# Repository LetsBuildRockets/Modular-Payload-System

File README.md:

# Cloning

This repo uses submodules. Be sure to clone the submodules as well as the repo:

```sh
git clone https://github.com/LetsBuildRockets/Modular-Payload-System/
cd Modular-Payload-System
git submodule update --init --recursive
```

# Specifications

The Modular Payload System specifications can be found [here](https://github.com/LetsBuildRockets/Modular-Payload-System/blob/master/Hardware/Reference/Specifications.md).

# Modules

A list of modules can be found [here](https://github.com/LetsBuildRockets/Modular-Payload-System/blob/master/ModuleList.md).

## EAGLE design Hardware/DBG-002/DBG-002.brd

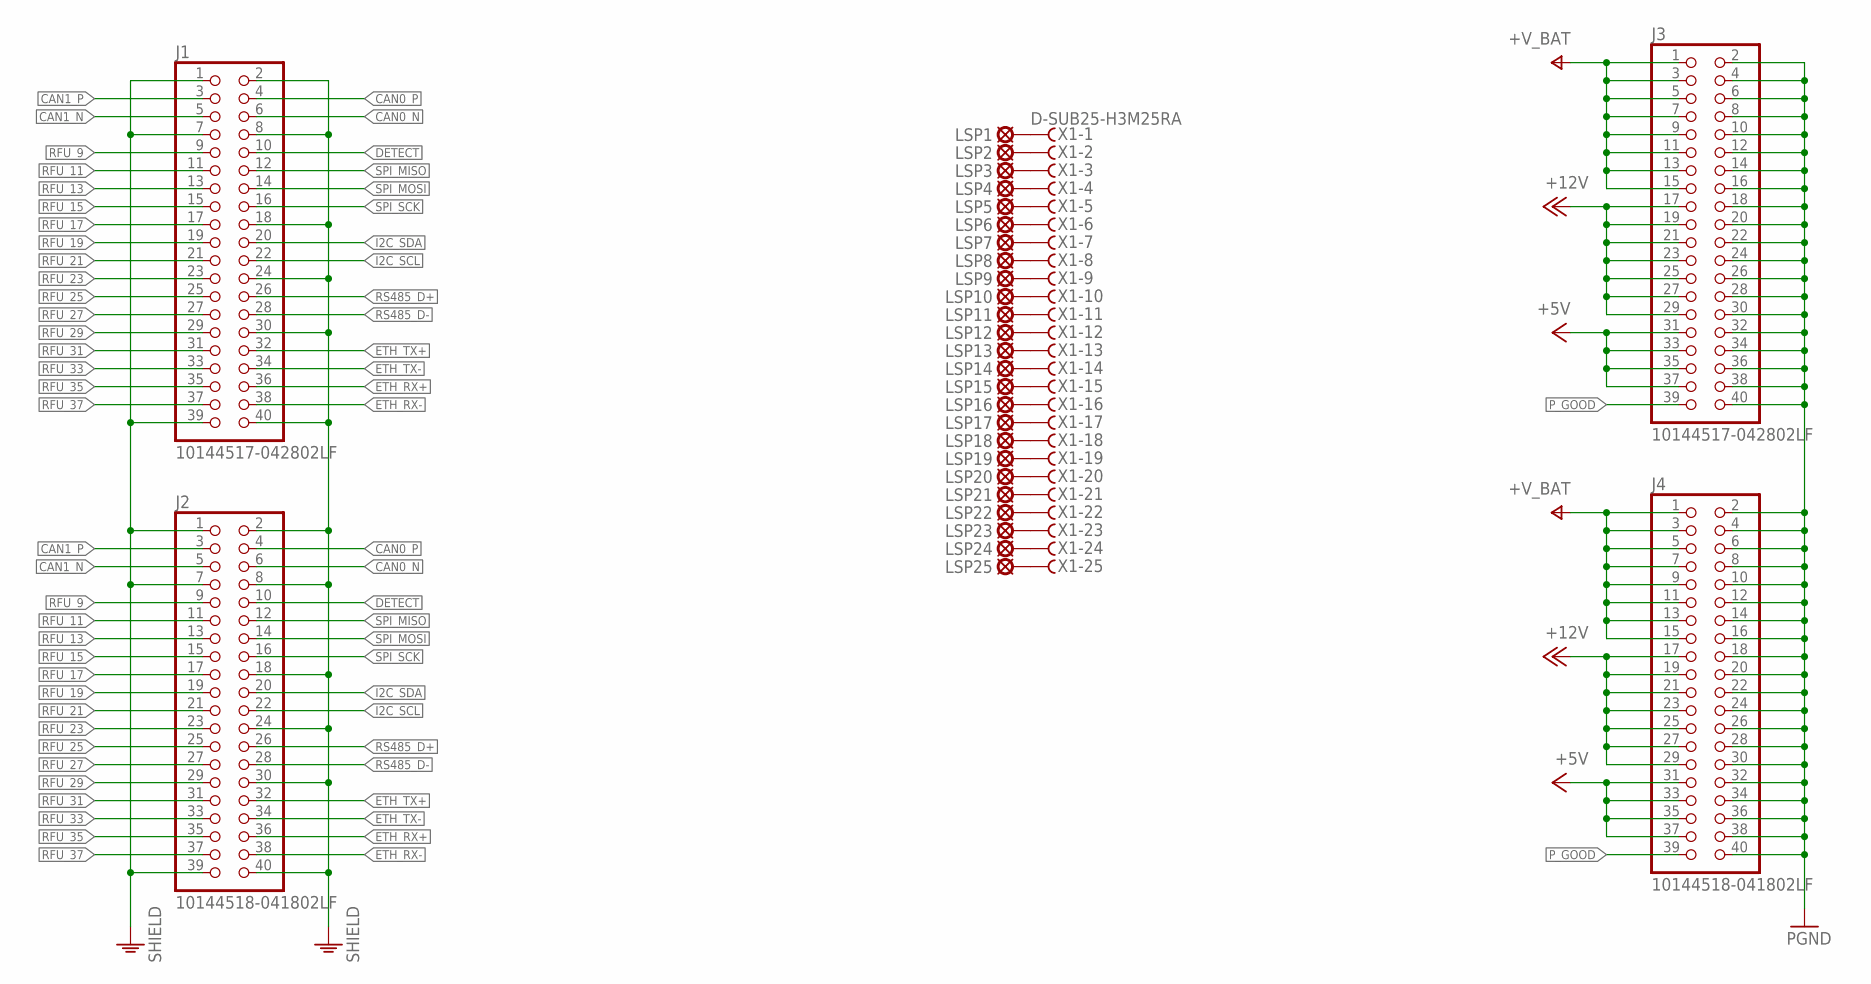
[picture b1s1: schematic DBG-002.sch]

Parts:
J1, J3: 10144517-042802LF
J2, J4: 10144518-041802LF
LSP1, LSP2, LSP3, LSP4, LSP5, LSP6, LSP7, LSP8, LSP9, LSP10, LSP11, LSP12, LSP13, LSP14, LSP15, LSP16, LSP17, LSP18, LSP19, LSP20, LSP21, LSP22, LSP23, LSP24, LSP25: LSP11
X1: D-SUB25-H3M25RA; H3M25RA

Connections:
+5V: J3.31, J3.33, J3.35, J3.37, J4.31, J4.33, J4.35, J4.37
+12V: J3.17, J3.19, J3.21, J3.23, J3.25, J3.27, J3.29, J4.17, J4.19, J4.21, J4.23, J4.25, J4.27, J4.29
+V_BAT: J3.1, J3.3, J3.5, J3.7, J3.9, J3.11, J3.13, J3.15, J4.1, J4.3, J4.5, J4.7, J4.9, J4.11, J4.13, J4.15
CAN0_N: J1.6, J2.6
CAN0_P: J1.4, J2.4
CAN1_N: J1.5, J2.5
CAN1_P: J1.3, J2.3
DETECT: J1.10, J2.10
ETH_RX+: J1.36, J2.36
ETH_RX-: J1.38, J2.38
ETH_TX+: J1.32, J2.32
ETH_TX-: J1.34, J2.34
I2C_SCL: J1.22, J2.22
I2C_SDA: J1.20, J2.20
unnamed: LSP1.MP, X1.1
unnamed: LSP2.MP, X1.2
unnamed: LSP3.MP, X1.3
unnamed: LSP4.MP, X1.4
unnamed: LSP5.MP, X1.5
unnamed: LSP6.MP, X1.6
unnamed: LSP7.MP, X1.7
unnamed: LSP8.MP, X1.8
unnamed: LSP9.MP, X1.9
unnamed: LSP10.MP, X1.10
unnamed: LSP11.MP, X1.11
unnamed: LSP12.MP, X1.12
unnamed: LSP13.MP, X1.13
unnamed: LSP14.MP, X1.14
unnamed: LSP15.MP, X1.15
unnamed: LSP16.MP, X1.16
unnamed: LSP17.MP, X1.17
unnamed: LSP18.MP, X1.18
unnamed: LSP19.MP, X1.19
unnamed: LSP20.MP, X1.20
unnamed: LSP21.MP, X1.21
unnamed: LSP22.MP, X1.22
unnamed: LSP23.MP, X1.23
unnamed: LSP24.MP, X1.24
unnamed: LSP25.MP, X1.25
PGND: J3.2, J3.4, J3.6, J3.8, J3.10, J3.12, J3.14, J3.16, J3.18, J3.20, J3.22, J3.24, J3.26, J3.28, J3.30, J3.32, J3.34, J3.36, J3.38, J3.40, J4.2, J4.4, J4.6, J4.8, J4.10, J4.12, J4.14, J4.16, J4.18, J4.20, J4.22, J4.24, J4.26, J4.28, J4.30, J4.32, J4.34, J4.36, J4.38, J4.40
P_GOOD: J3.39, J4.39
RFU_9: J1.9, J2.9
RFU_11: J1.11, J2.11
RFU_13: J1.13, J2.13
RFU_15: J1.15, J2.15
RFU_17: J1.17, J2.17
RFU_19: J1.19, J2.19
RFU_21: J1.21, J2.21
RFU_23: J1.23, J2.23
RFU_25: J1.25, J2.25
RFU_27: J1.27, J2.27
RFU_29: J1.29, J2.29
RFU_31: J1.31, J2.31
RFU_33: J1.33, J2.33
RFU_35: J1.35, J2.35
RFU_37: J1.37, J2.37
RS485_D+: J1.26, J2.26
RS485_D-: J1.28, J2.28
SHIELD: J1.1, J1.2, J1.7, J1.8, J1.18, J1.24, J1.30, J1.39, J1.40, J2.1, J2.2, J2.7, J2.8, J2.18, J2.24, J2.30, J2.39, J2.40
SPI_MISO: J1.12, J2.12
SPI_MOSI: J1.14, J2.14
SPI_SCK: J1.16, J2.16

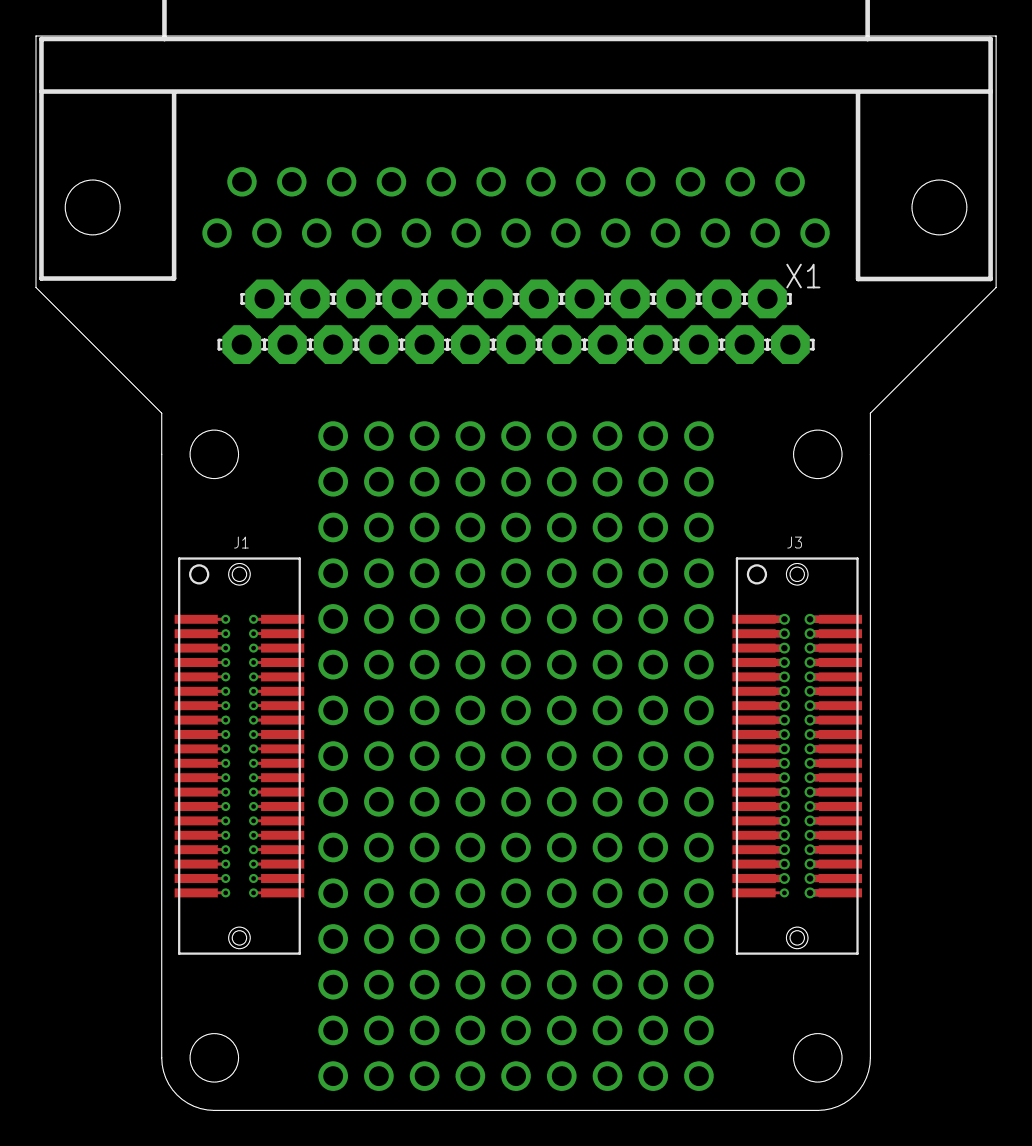
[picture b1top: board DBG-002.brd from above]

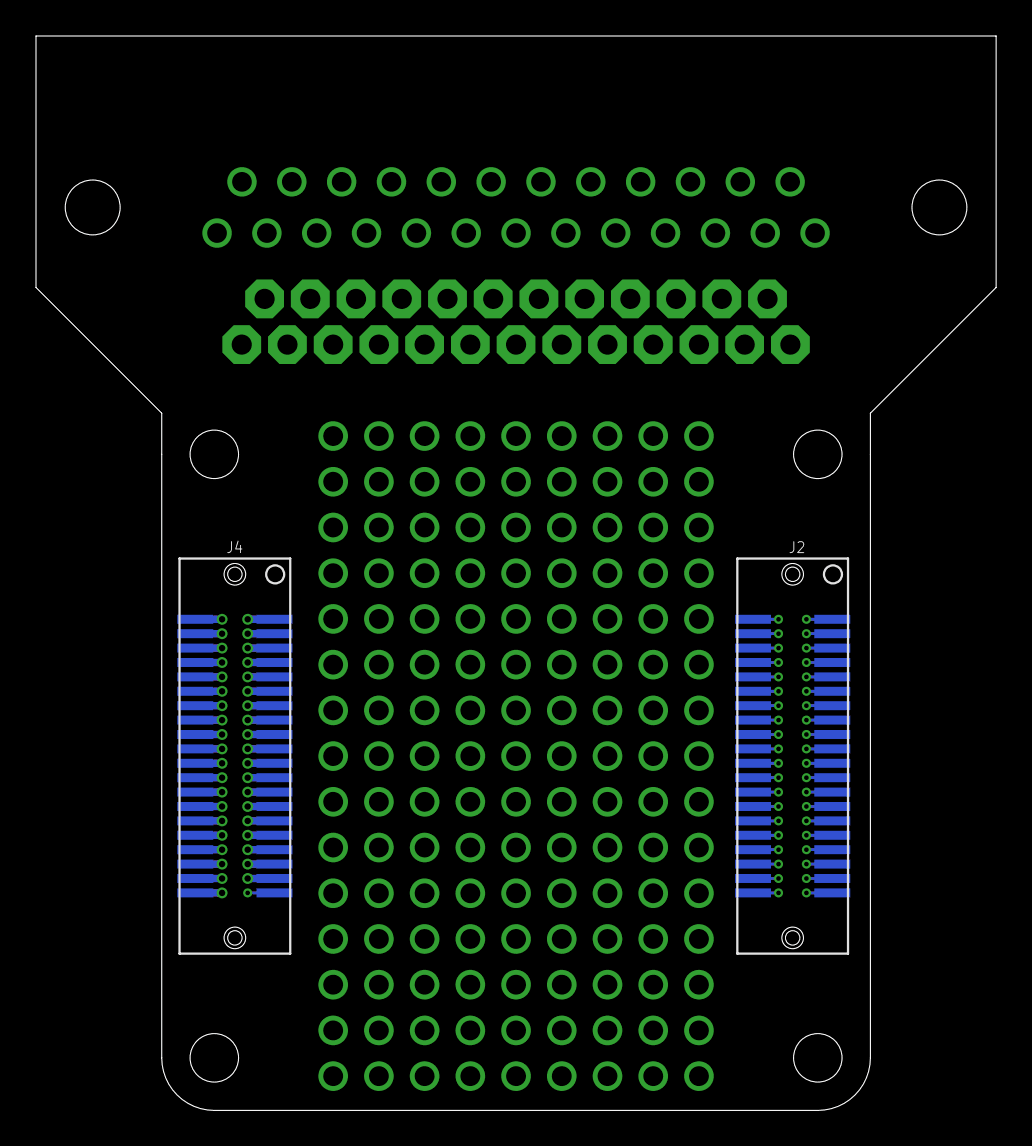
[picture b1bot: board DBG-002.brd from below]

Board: 2 copper layers, 53.3 x 59.7 mm, 30 parts (2 on the bottom side), 62 nets.

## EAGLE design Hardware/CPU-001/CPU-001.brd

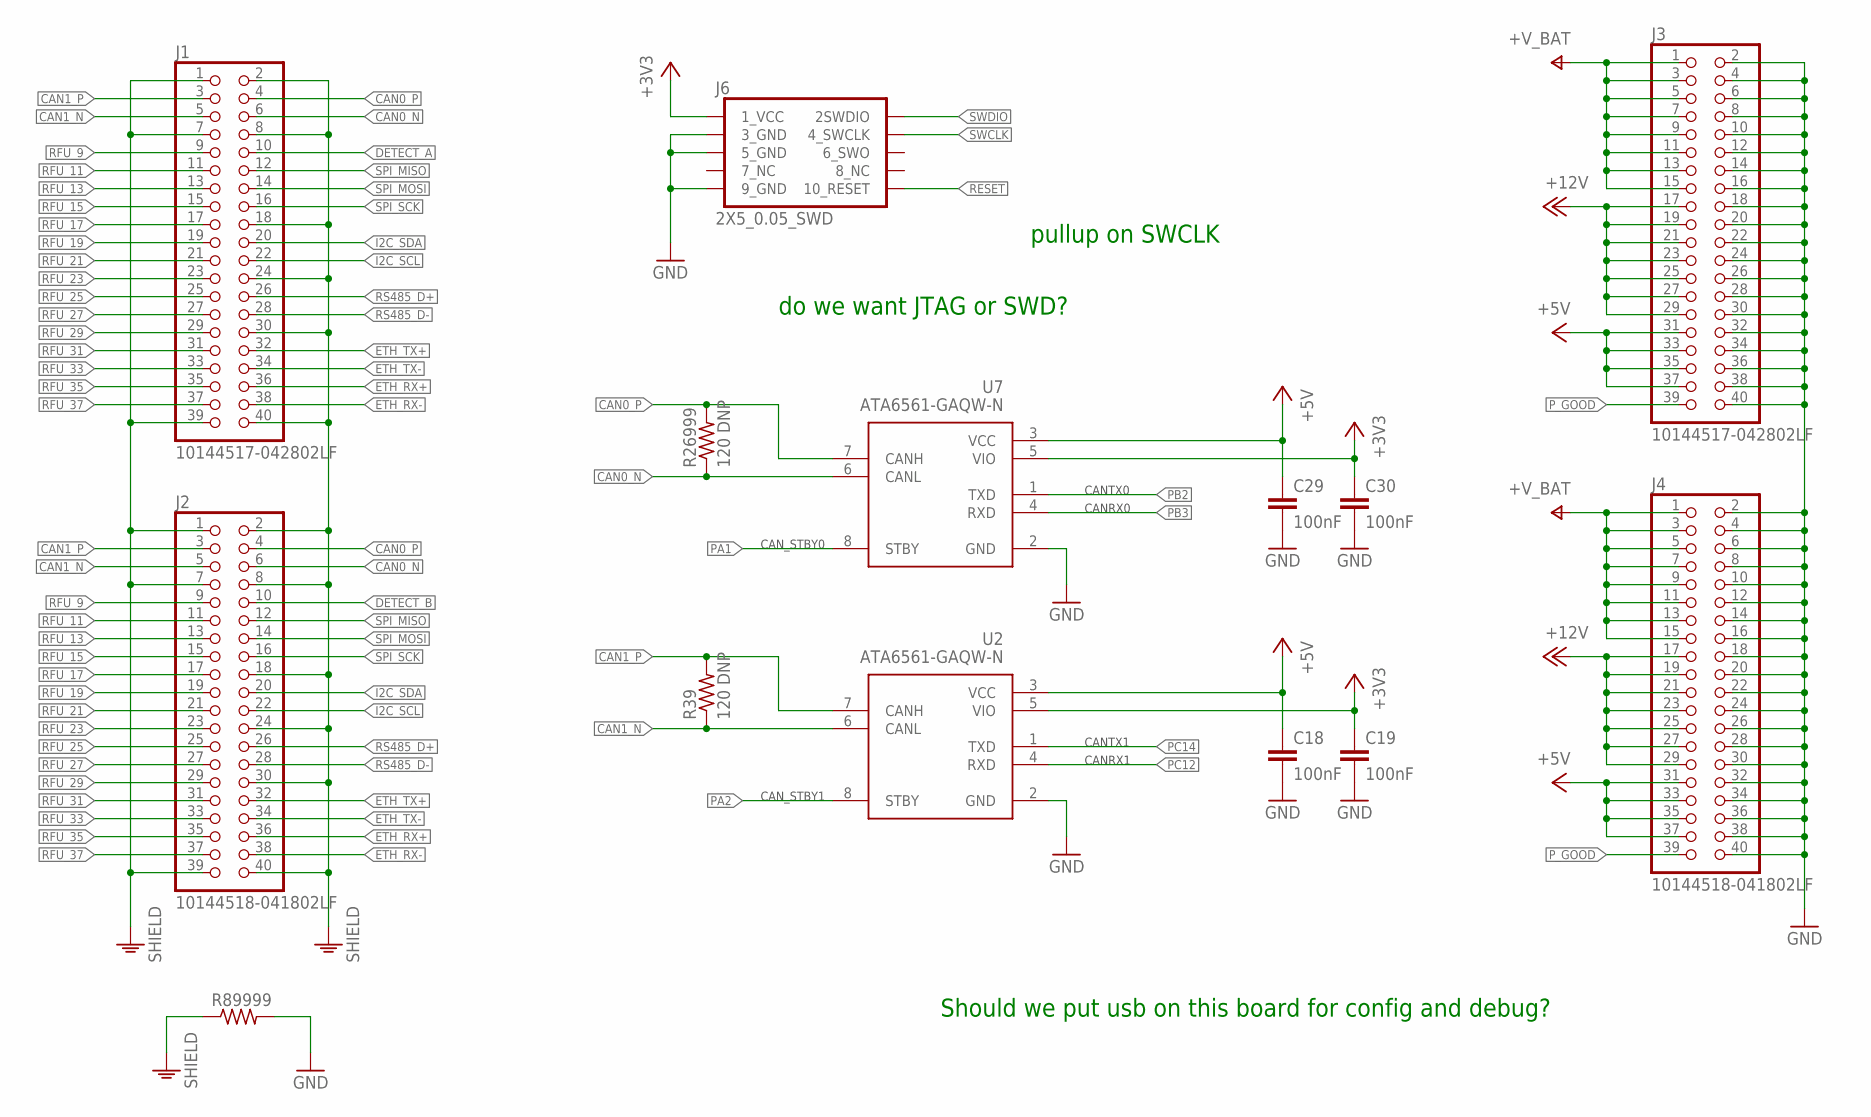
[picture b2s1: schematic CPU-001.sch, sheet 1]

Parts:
C18, C19, C29, C30: 100nF; C0402
J1, J3: 10144517-042802LF
J2, J4: 10144518-041802LF
J6: 2X5_0.05_SWD; 2X5_RIGHT
R39, R26999: 120 DNP; R0402
R89999: R-US_R0402; R0402
U2, U7: ATA6561-GAQW-N; SOIC127P600X175-8N

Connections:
+3V3: C19.1, C30.1, J6.1 (1_VCC), U2.5 (VIO), U7.5 (VIO); also elsewhere on the board
+5V: C18.1, C29.1, J3.31, J3.33, J3.35, J3.37, J4.31, J4.33, J4.35, J4.37, U2.3 (VCC), U7.3 (VCC); also elsewhere on the board
+12V: J3.17, J3.19, J3.21, J3.23, J3.25, J3.27, J3.29, J4.17, J4.19, J4.21, J4.23, J4.25, J4.27, J4.29
+V_BAT: J3.1, J3.3, J3.5, J3.7, J3.9, J3.11, J3.13, J3.15, J4.1, J4.3, J4.5, J4.7, J4.9, J4.11, J4.13, J4.15
CAN0_N: J1.6, J2.6, R26999.1, U7.6 (CANL)
CAN0_P: J1.4, J2.4, R26999.2, U7.7 (CANH)
CAN1_N: J1.5, J2.5, R39.1, U2.6 (CANL)
CAN1_P: J1.3, J2.3, R39.2, U2.7 (CANH)
DETECT_A: J1.10
DETECT_B: J2.10
ETH_RX+: J1.36, J2.36
ETH_RX-: J1.38, J2.38
ETH_TX+: J1.32, J2.32
ETH_TX-: J1.34, J2.34
GND: C18.2, C19.2, C29.2, C30.2, J3.2, J3.4, J3.6, J3.8, J3.10, J3.12, J3.14, J3.16, J3.18, J3.20, J3.22, J3.24, J3.26, J3.28, J3.30, J3.32, J3.34, J3.36, J3.38, J3.40, J4.2, J4.4, J4.6, J4.8, J4.10, J4.12, J4.14, J4.16, J4.18, J4.20, J4.22, J4.24, J4.26, J4.28, J4.30, J4.32, J4.34, J4.36, J4.38, J4.40, J6.3 (3_GND), J6.5 (5_GND), J6.9 (9_GND), R89999.2, U2.2 (GND), U7.2 (GND); also elsewhere on the board
I2C_SCL: J1.22, J2.22
I2C_SDA: J1.20, J2.20
PA1: U7.8 (STBY); also elsewhere on the board
PA2: U2.8 (STBY); also elsewhere on the board
PB2: U7.1 (TXD); also elsewhere on the board
PB3: U7.4 (RXD); also elsewhere on the board
PC12: U2.4 (RXD); also elsewhere on the board
PC14: U2.1 (TXD); also elsewhere on the board
P_GOOD: J3.39, J4.39
RESET: J6.10 (10_RESET)
RFU_9: J1.9, J2.9
RFU_11: J1.11, J2.11
RFU_13: J1.13, J2.13
RFU_15: J1.15, J2.15
RFU_17: J1.17, J2.17
RFU_19: J1.19, J2.19
RFU_21: J1.21, J2.21
RFU_23: J1.23, J2.23
RFU_25: J1.25, J2.25
RFU_27: J1.27, J2.27
RFU_29: J1.29, J2.29
RFU_31: J1.31, J2.31
RFU_33: J1.33, J2.33
RFU_35: J1.35, J2.35
RFU_37: J1.37, J2.37
RS485_D+: J1.26, J2.26
RS485_D-: J1.28, J2.28
SHIELD: J1.1, J1.2, J1.7, J1.8, J1.18, J1.24, J1.30, J1.39, J1.40, J2.1, J2.2, J2.7, J2.8, J2.18, J2.24, J2.30, J2.39, J2.40, R89999.1
SPI_MISO: J1.12, J2.12
SPI_MOSI: J1.14, J2.14
SPI_SCK: J1.16, J2.16
SWCLK: J6.4 (4_SWCLK)
SWDIO: J6.2 (2SWDIO)

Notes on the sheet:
do we want JTAG or SWD?
Should we put usb on this board for config and debug?
pullup on SWCLK
CAN_STBY0
CAN_STBY1
CANTX0
CANRX0
CANRX1
CANTX1

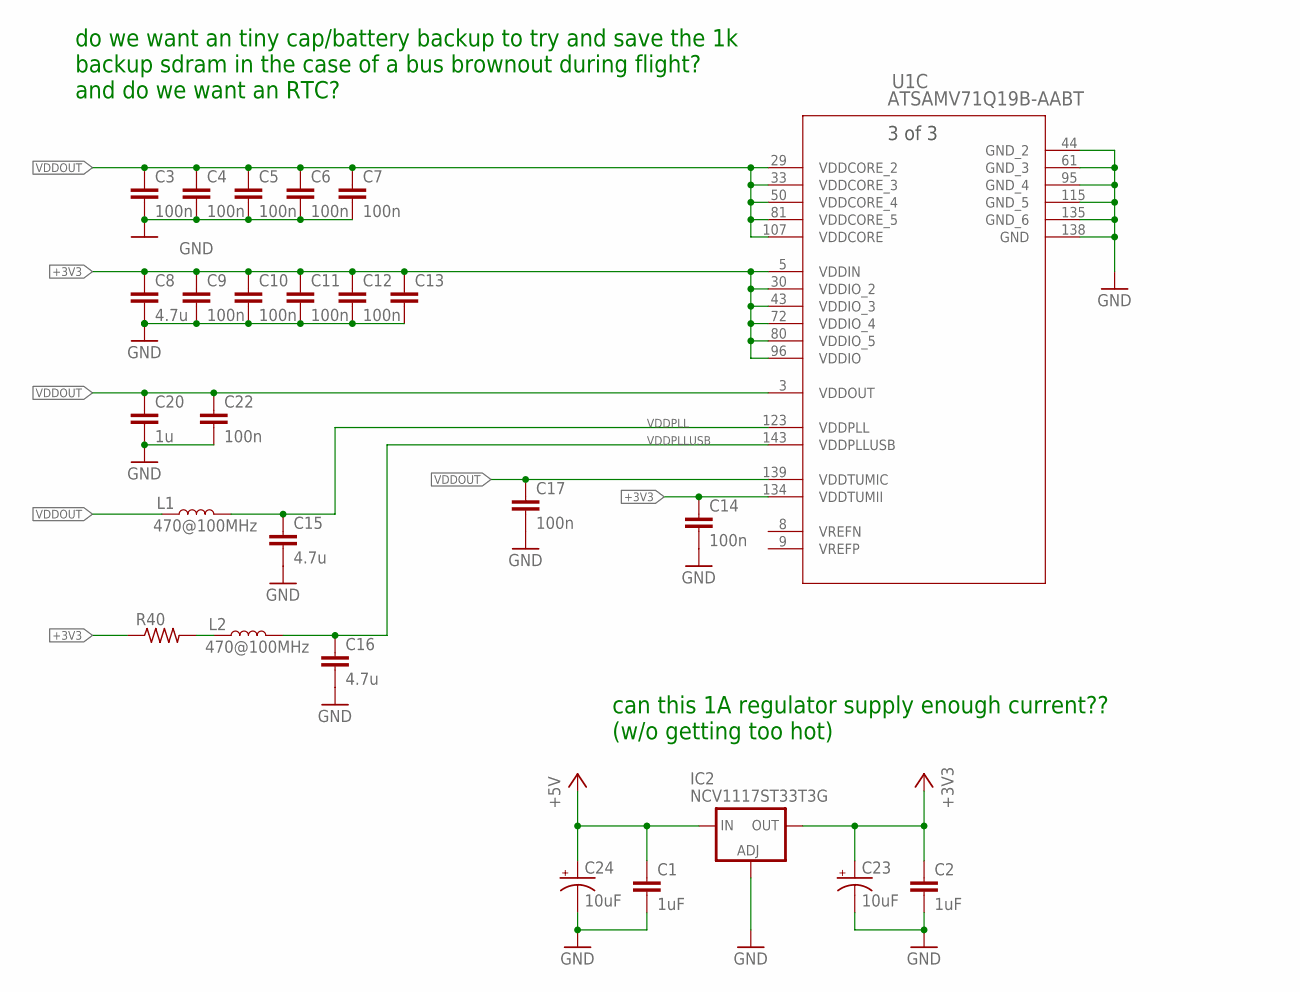
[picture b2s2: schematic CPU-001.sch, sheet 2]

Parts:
C1, C2: 1uF; C0603
C3, C4, C5, C6, C7, C9, C10, C11, C12, C13, C14, C17, C22: 100n; C0402
C8, C15, C16: 4.7u; C0805
C20: 1u; C0402
C23, C24: 10uF; 0603-POLAR
IC2: NCV1117ST33T3G; SOT223
L1, L2: 470@100MHz; 0603
R40: R-US_R0402; R0402
U1: ATSAMV71Q19B-AABT; LQFP144_20X20MC

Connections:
+3V3: C2.1, C8.1, C9.1, C10.1, C11.1, C12.1, C13.1, C14.1, C23.+, IC2.4 (OUT), R40.1, U1.5 (VDDIN), U1.30 (VDDIO_2), U1.43 (VDDIO_3), U1.72 (VDDIO_4), U1.80 (VDDIO_5), U1.96 (VDDIO), U1.134 (VDDTUMII); also elsewhere on the board
+5V: C1.1, C24.+, IC2.3 (IN); also elsewhere on the board
GND: C1.2, C2.2, C3.2, C4.2, C5.2, C6.2, C7.2, C8.2, C9.2, C10.2, C11.2, C12.2, C13.2, C14.2, C15.2, C16.2, C17.2, C20.2, C22.2, C23.-, C24.-, IC2.1 (ADJ), U1.44 (GND_2), U1.61 (GND_3), U1.95 (GND_4), U1.115 (GND_5), U1.135 (GND_6), U1.138 (GND); also elsewhere on the board
unnamed: L2.1, R40.2
VDDOUT: C3.1, C4.1, C5.1, C6.1, C7.1, C17.1, C20.1, C22.1, L1.1, U1.3 (VDDOUT), U1.29 (VDDCORE_2), U1.33 (VDDCORE_3), U1.50 (VDDCORE_4), U1.81 (VDDCORE_5), U1.107 (VDDCORE), U1.139 (VDDTUMIC)
VDDPLL: C15.1, L1.2, U1.123 (VDDPLL)
VDDPLLUSB: C16.1, L2.2, U1.143 (VDDPLLUSB)
VREFN: U1.8 (VREFN)
VREFP: U1.9 (VREFP)

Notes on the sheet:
can this 1A regulator supply enough current?? (w/o getting too hot)
do we want an tiny cap/battery backup to try and save the 1k backup sdram in the case of a bus brownout during flight? and do we want an RTC?

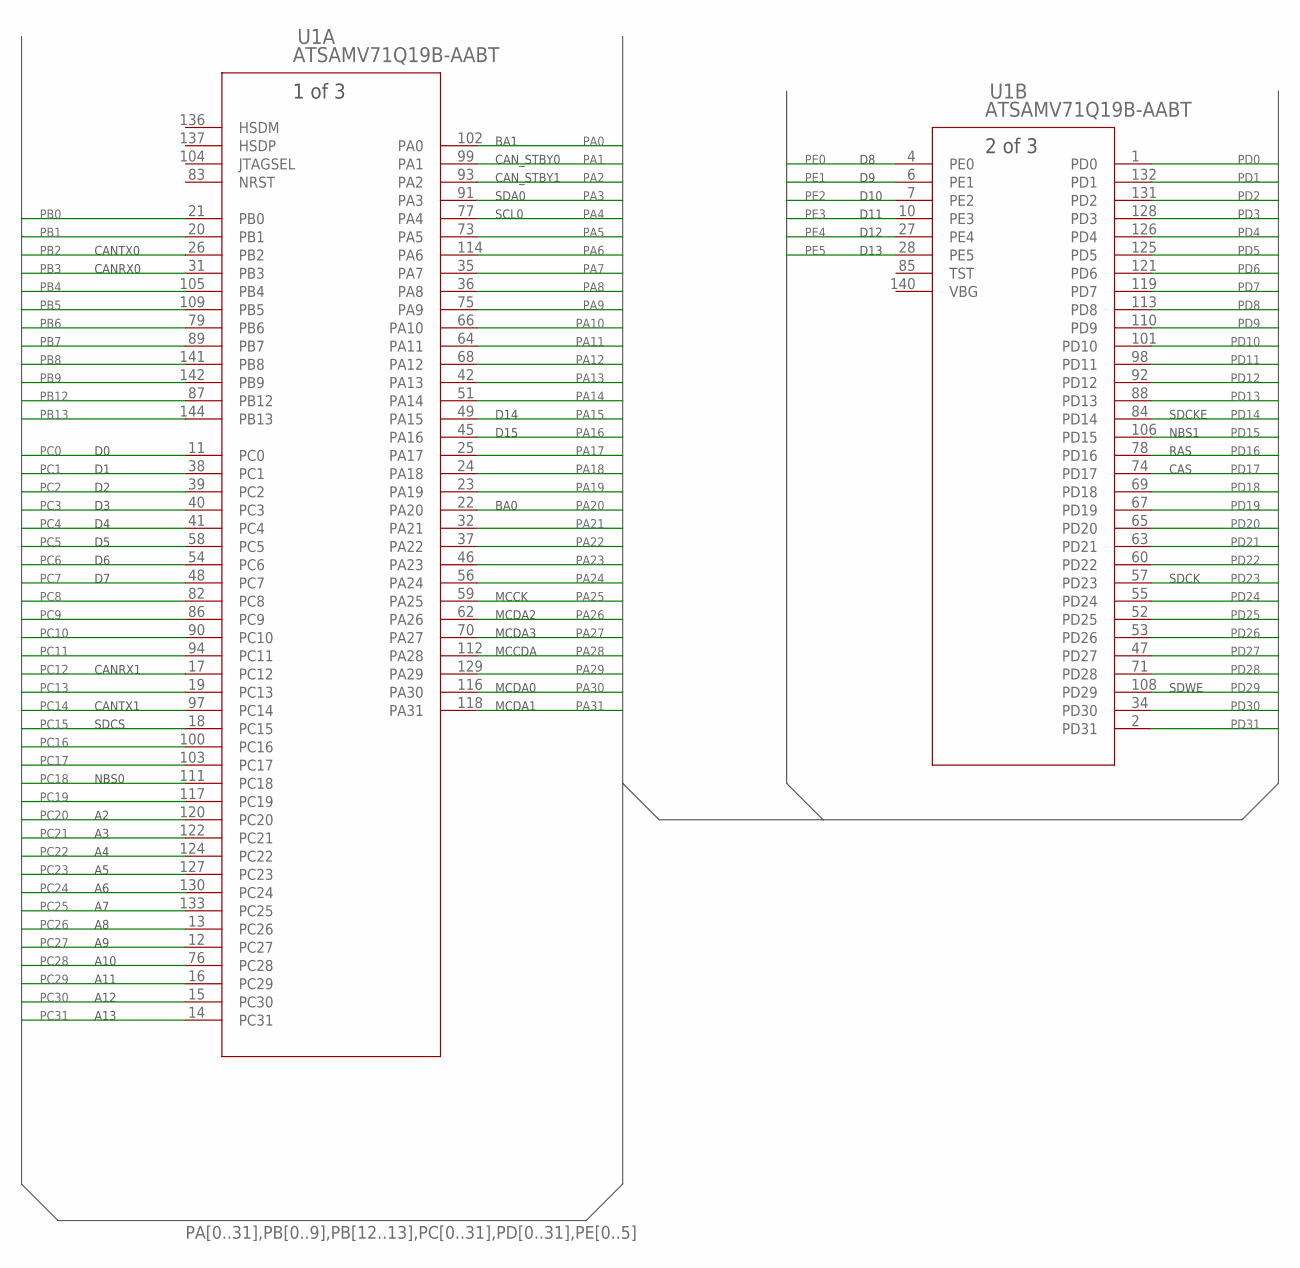
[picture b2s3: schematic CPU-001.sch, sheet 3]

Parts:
U1: ATSAMV71Q19B-AABT; LQFP144_20X20MC

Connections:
PA0: U1.102 (PA0); also elsewhere on the board
PA1: U1.99 (PA1); also elsewhere on the board
PA2: U1.93 (PA2); also elsewhere on the board
PA3: U1.91 (PA3); also elsewhere on the board
PA4: U1.77 (PA4); also elsewhere on the board
PA5: U1.73 (PA5)
PA6: U1.114 (PA6)
PA7: U1.35 (PA7)
PA8: U1.36 (PA8)
PA9: U1.75 (PA9)
PA10: U1.66 (PA10)
PA11: U1.64 (PA11)
PA12: U1.68 (PA12)
PA13: U1.42 (PA13)
PA14: U1.51 (PA14)
PA15: U1.49 (PA15); also elsewhere on the board
PA16: U1.45 (PA16); also elsewhere on the board
PA17: U1.25 (PA17)
PA18: U1.24 (PA18)
PA19: U1.23 (PA19)
PA20: U1.22 (PA20); also elsewhere on the board
PA21: U1.32 (PA21)
PA22: U1.37 (PA22)
PA23: U1.46 (PA23)
PA24: U1.56 (PA24)
PA25: U1.59 (PA25); also elsewhere on the board
PA26: U1.62 (PA26); also elsewhere on the board
PA27: U1.70 (PA27); also elsewhere on the board
PA28: U1.112 (PA28); also elsewhere on the board
PA29: U1.129 (PA29)
PA30: U1.116 (PA30); also elsewhere on the board
PA31: U1.118 (PA31); also elsewhere on the board
PB0: U1.21 (PB0)
PB1: U1.20 (PB1)
PB2: U1.26 (PB2); also elsewhere on the board
PB3: U1.31 (PB3); also elsewhere on the board
PB4: U1.105 (PB4)
PB5: U1.109 (PB5)
PB6: U1.79 (PB6)
PB7: U1.89 (PB7)
PB8: U1.141 (PB8)
PB9: U1.142 (PB9)
PB12: U1.87 (PB12)
PB13: U1.144 (PB13)
PC0: U1.11 (PC0); also elsewhere on the board
PC1: U1.38 (PC1); also elsewhere on the board
PC2: U1.39 (PC2); also elsewhere on the board
PC3: U1.40 (PC3); also elsewhere on the board
PC4: U1.41 (PC4); also elsewhere on the board
PC5: U1.58 (PC5); also elsewhere on the board
PC6: U1.54 (PC6); also elsewhere on the board
PC7: U1.48 (PC7); also elsewhere on the board
PC8: U1.82 (PC8)
PC9: U1.86 (PC9)
PC10: U1.90 (PC10)
PC11: U1.94 (PC11)
PC12: U1.17 (PC12); also elsewhere on the board
PC13: U1.19 (PC13)
PC14: U1.97 (PC14); also elsewhere on the board
PC15: U1.18 (PC15); also elsewhere on the board
PC16: U1.100 (PC16)
PC17: U1.103 (PC17)
PC18: U1.111 (PC18); also elsewhere on the board
PC19: U1.117 (PC19)
PC20: U1.120 (PC20); also elsewhere on the board
PC21: U1.122 (PC21); also elsewhere on the board
PC22: U1.124 (PC22); also elsewhere on the board
PC23: U1.127 (PC23); also elsewhere on the board
PC24: U1.130 (PC24); also elsewhere on the board
PC25: U1.133 (PC25); also elsewhere on the board
PC26: U1.13 (PC26); also elsewhere on the board
PC27: U1.12 (PC27); also elsewhere on the board
PC28: U1.76 (PC28); also elsewhere on the board
PC29: U1.16 (PC29); also elsewhere on the board
PC30: U1.15 (PC30); also elsewhere on the board
PC31: U1.14 (PC31); also elsewhere on the board
PD0: U1.1 (PD0)
PD1: U1.132 (PD1)
PD2: U1.131 (PD2)
PD3: U1.128 (PD3)
PD4: U1.126 (PD4)
PD5: U1.125 (PD5)
PD6: U1.121 (PD6)
PD7: U1.119 (PD7)
PD8: U1.113 (PD8)
PD9: U1.110 (PD9)
PD10: U1.101 (PD10)
PD11: U1.98 (PD11)
PD12: U1.92 (PD12)
PD13: U1.88 (PD13)
PD14: U1.84 (PD14); also elsewhere on the board
PD15: U1.106 (PD15); also elsewhere on the board
PD16: U1.78 (PD16); also elsewhere on the board
PD17: U1.74 (PD17); also elsewhere on the board
PD18: U1.69 (PD18)
PD19: U1.67 (PD19)
PD20: U1.65 (PD20)
PD21: U1.63 (PD21)
PD22: U1.60 (PD22)
PD23: U1.57 (PD23); also elsewhere on the board
PD24: U1.55 (PD24)
PD25: U1.52 (PD25)
PD26: U1.53 (PD26)
PD27: U1.47 (PD27)
PD28: U1.71 (PD28)
PD29: U1.108 (PD29); also elsewhere on the board
PD30: U1.34 (PD30)
PD31: U1.2 (PD31)
PE0: U1.4 (PE0); also elsewhere on the board
PE1: U1.6 (PE1); also elsewhere on the board
PE2: U1.7 (PE2); also elsewhere on the board
PE3: U1.10 (PE3); also elsewhere on the board
PE4: U1.27 (PE4); also elsewhere on the board
PE5: U1.28 (PE5); also elsewhere on the board
VREFN: U1.8 (VREFN)
VREFP: U1.9 (VREFP)

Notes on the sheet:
NBS0
A10
A11
A12
A13
BA0
BA1
D10
D11
D12
D13
D14
D15
SDCK
SDCKE
NBS1
SDWE
CAS
RAS
SDCS
CANTX0
CANRX0
CANTX1
CANRX1
MCCK
MCDA2
MCDA3
MCCDA
MCDA0
MCDA1
CAN_STBY0
CAN_STBY1
SCL0
SDA0

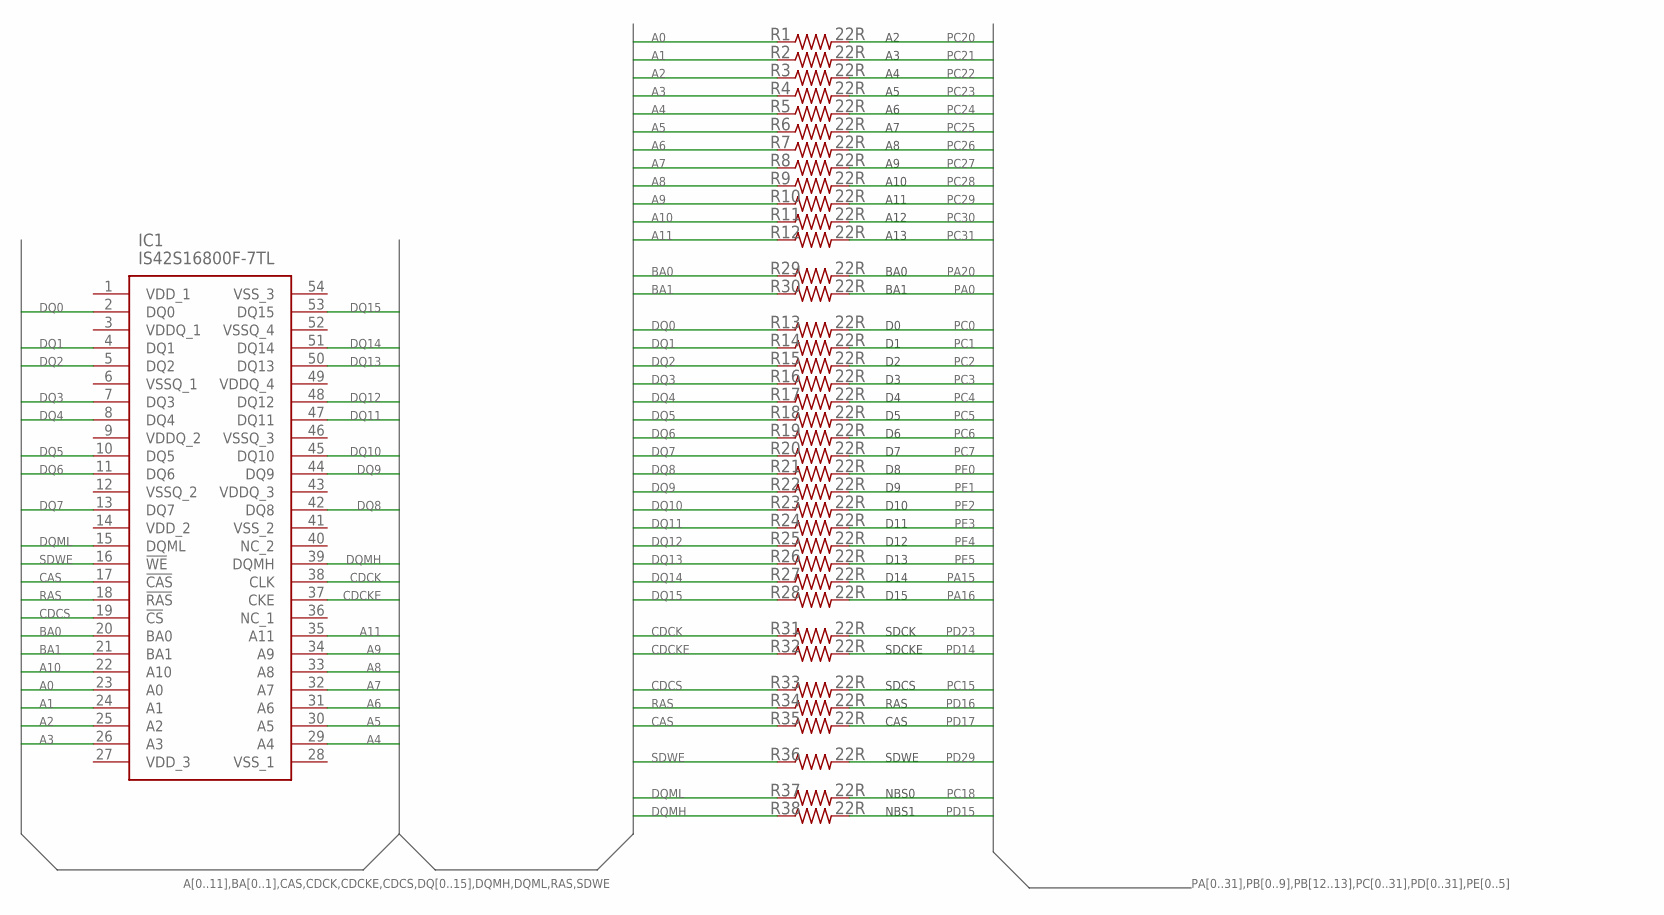
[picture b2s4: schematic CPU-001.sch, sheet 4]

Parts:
IC1: IS42S16800F-7TL; SOP80P1176X120-54N
R1, R2, R3, R4, R5, R6, R7, R8, R9, R10, R11, R12, R13, R14, R15, R16, R17, R18, R19, R20, R21, R22, R23, R24, R25, R26, R27, R28, R29, R30, R31, R32, R33, R34, R35, R36, R37, R38: 22R; R0402

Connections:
+3V3: IC1.1 (VDD_1), IC1.3 (VDDQ_1), IC1.9 (VDDQ_2), IC1.14 (VDD_2), IC1.27 (VDD_3), IC1.43 (VDDQ_3), IC1.49 (VDDQ_4); also elsewhere on the board
A0: IC1.23 (A0), R1.1
A1: IC1.24 (A1), R2.1
A2: IC1.25 (A2), R3.1
A3: IC1.26 (A3), R4.1
A4: IC1.29 (A4), R5.1
A5: IC1.30 (A5), R6.1
A6: IC1.31 (A6), R7.1
A7: IC1.32 (A7), R8.1
A8: IC1.33 (A8), R9.1
A9: IC1.34 (A9), R10.1
A10: IC1.22 (A10), R11.1
A11: IC1.35 (A11), R12.1
BA0: IC1.20 (BA0), R29.1
BA1: IC1.21 (BA1), R30.1
CAS: IC1.17 (!CAS), R35.1
CDCK: IC1.38 (CLK), R31.1
CDCKE: IC1.37 (CKE), R32.1
CDCS: IC1.19 (!CS), R33.1
DQ0: IC1.2 (DQ0), R13.1
DQ1: IC1.4 (DQ1), R14.1
DQ2: IC1.5 (DQ2), R15.1
DQ3: IC1.7 (DQ3), R16.1
DQ4: IC1.8 (DQ4), R17.1
DQ5: IC1.10 (DQ5), R18.1
DQ6: IC1.11 (DQ6), R19.1
DQ7: IC1.13 (DQ7), R20.1
DQ8: IC1.42 (DQ8), R21.1
DQ9: IC1.44 (DQ9), R22.1
DQ10: IC1.45 (DQ10), R23.1
DQ11: IC1.47 (DQ11), R24.1
DQ12: IC1.48 (DQ12), R25.1
DQ13: IC1.50 (DQ13), R26.1
DQ14: IC1.51 (DQ14), R27.1
DQ15: IC1.53 (DQ15), R28.1
DQMH: IC1.39 (DQMH), R38.1
DQML: IC1.15 (DQML), R37.1
GND: IC1.6 (VSSQ_1), IC1.12 (VSSQ_2), IC1.28 (VSS_1), IC1.41 (VSS_2), IC1.46 (VSSQ_3), IC1.52 (VSSQ_4), IC1.54 (VSS_3); also elsewhere on the board
PA0: R30.2; also elsewhere on the board
PA15: R27.2; also elsewhere on the board
PA16: R28.2; also elsewhere on the board
PA20: R29.2; also elsewhere on the board
PC0: R13.2; also elsewhere on the board
PC1: R14.2; also elsewhere on the board
PC2: R15.2; also elsewhere on the board
PC3: R16.2; also elsewhere on the board
PC4: R17.2; also elsewhere on the board
PC5: R18.2; also elsewhere on the board
PC6: R19.2; also elsewhere on the board
PC7: R20.2; also elsewhere on the board
PC15: R33.2; also elsewhere on the board
PC18: R37.2; also elsewhere on the board
PC20: R1.2; also elsewhere on the board
PC21: R2.2; also elsewhere on the board
PC22: R3.2; also elsewhere on the board
PC23: R4.2; also elsewhere on the board
PC24: R5.2; also elsewhere on the board
PC25: R6.2; also elsewhere on the board
PC26: R7.2; also elsewhere on the board
PC27: R8.2; also elsewhere on the board
PC28: R9.2; also elsewhere on the board
PC29: R10.2; also elsewhere on the board
PC30: R11.2; also elsewhere on the board
PC31: R12.2; also elsewhere on the board
PD14: R32.2; also elsewhere on the board
PD15: R38.2; also elsewhere on the board
PD16: R34.2; also elsewhere on the board
PD17: R35.2; also elsewhere on the board
PD23: R31.2; also elsewhere on the board
PD29: R36.2; also elsewhere on the board
PE0: R21.2; also elsewhere on the board
PE1: R22.2; also elsewhere on the board
PE2: R23.2; also elsewhere on the board
PE3: R24.2; also elsewhere on the board
PE4: R25.2; also elsewhere on the board
PE5: R26.2; also elsewhere on the board
RAS: IC1.18 (!RAS), R34.1
SDWE: IC1.16 (!WE), R36.1

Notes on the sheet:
A10
A11
A12
A13
BA0
BA1
D10
D11
D12
D13
D14
D15
SDCK
SDCKE
NBS1
NBS0
SDWE
CAS
RAS
SDCS

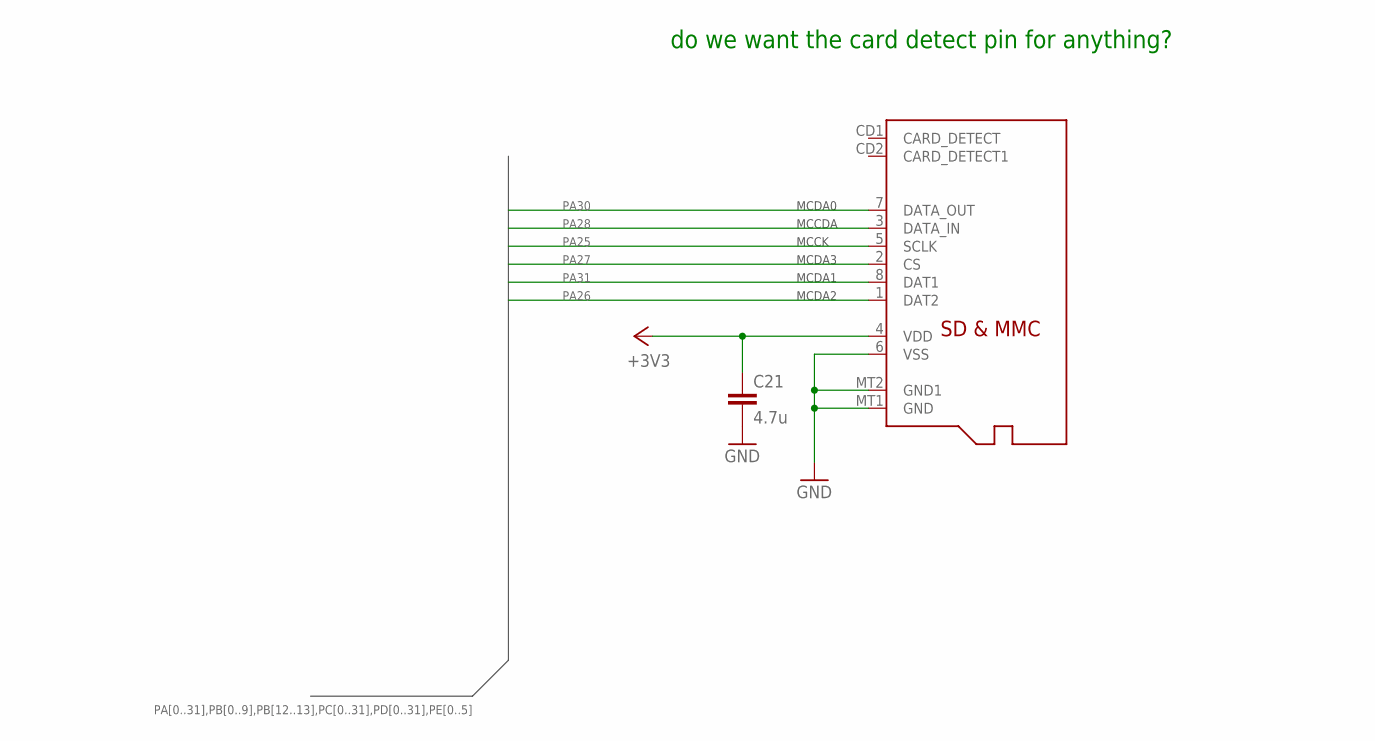
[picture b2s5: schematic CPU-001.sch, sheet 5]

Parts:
C21: 4.7u; C0805
U$5: MICROSD; MICROSD_

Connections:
+3V3: C21.1, U$5.4 (VDD); also elsewhere on the board
GND: C21.2, U$5.6 (VSS), U$5.MT1 (GND), U$5.MT2 (GND1); also elsewhere on the board
PA25: U$5.5 (SCLK); also elsewhere on the board
PA26: U$5.1 (DAT2); also elsewhere on the board
PA27: U$5.2 (CS); also elsewhere on the board
PA28: U$5.3 (DATA_IN); also elsewhere on the board
PA30: U$5.7 (DATA_OUT); also elsewhere on the board
PA31: U$5.8 (DAT1); also elsewhere on the board

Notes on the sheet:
MCCK
MCDA3
MCDA1
MCDA2
MCCDA
MCDA0
do we want the card detect pin for anything?

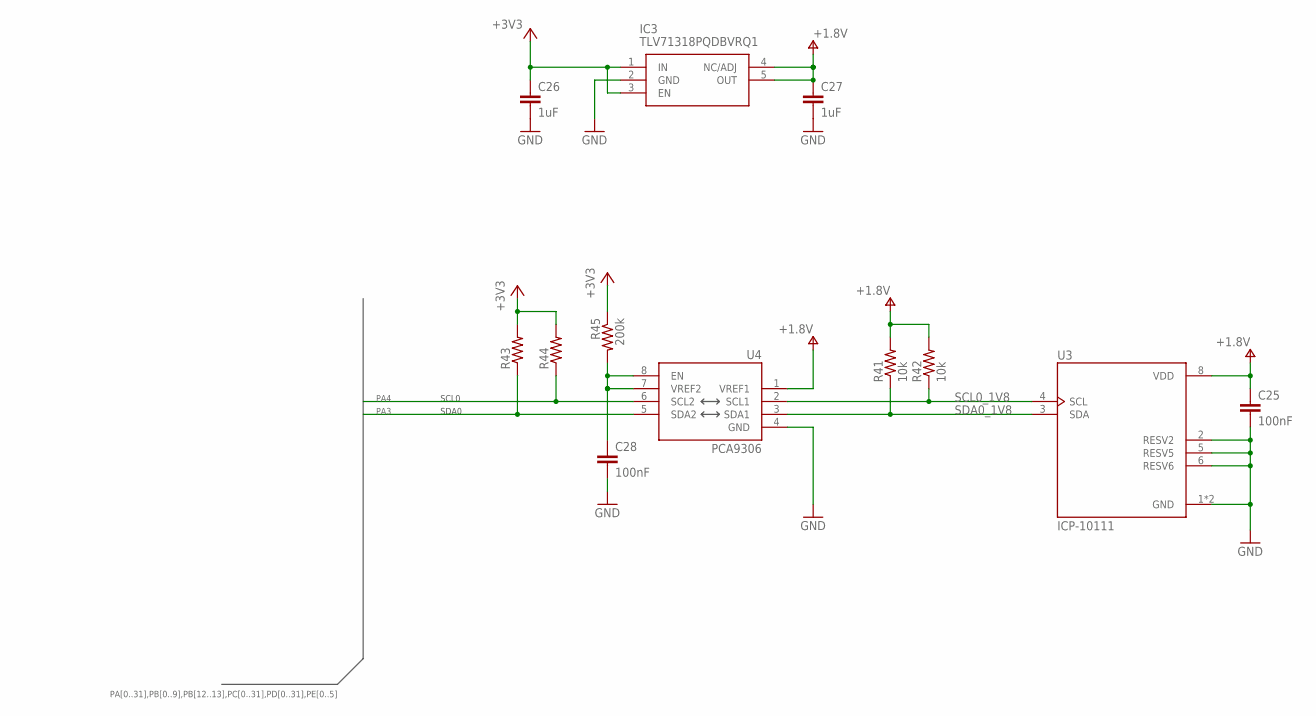
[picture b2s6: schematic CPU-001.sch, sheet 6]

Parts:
C25, C28: 100nF; C0402
C26, C27: 1uF; C0402
IC3: TLV71318PQDBVRQ1; SOT95P280X100-5N
R41, R42: 10k; R0402
R43, R44: R-US_R0402; R0402
R45: 200k; R0402
U3: ICP-10111; PSON65P250X200X100-8N
U4: PCA9306; PCA9306DC

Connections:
+1.8V: C25.1, C27.1, IC3.4 (NC/ADJ), IC3.5 (OUT), R41.2, R42.2, U3.8 (VDD), U4.1 (VREF1)
+3V3: C26.1, IC3.1 (IN), IC3.3 (EN), R43.2, R44.2, R45.1; also elsewhere on the board
GND: C25.2, C26.2, C27.2, C28.2, IC3.2 (GND), U3.1 (GND), U3.2 (RESV2), U3.5 (RESV5), U3.6 (RESV6), U3.7 (GND), U4.4 (GND); also elsewhere on the board
unnamed: C28.1, R45.2, U4.7 (VREF2), U4.8 (EN)
PA3: R43.1, U4.5 (SDA2); also elsewhere on the board
PA4: R44.1, U4.6 (SCL2); also elsewhere on the board
SCL0_1V8: R42.1, U3.4 (SCL), U4.2 (SCL1)
SDA0_1V8: R41.1, U3.3 (SDA), U4.3 (SDA1)

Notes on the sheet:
SDA0
SCL0

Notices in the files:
parts and their libraries:
SparkFun-Coils: Licensing: Creative Commons ShareAlike 4.0 International - https://creativecommons.org/licenses/by-sa/4.0
